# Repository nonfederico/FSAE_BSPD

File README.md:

# FSAE_BSPD
Schema per realizzare il componente BSPD "Brake system plausibility device" seguendo il regolamento di formula Student dell'anno 2024.  
Nel progetto utilizzo il circuito integrato "NE555" per attività universitaria.  
Gli spazi e le piste non sono ottimizzate.  
La documentazione è in italiano ma verrà tradotta in inglese

Schematic for building the BSPD "Brake System Plausibility Device" component according to the Formula Student 2024 regulations. 
In the project, i use the integrated circuit "NE555" for academic activities.
PCB Traces and spaces are not optimized.
The documentation is in Italian but will be translated into English.

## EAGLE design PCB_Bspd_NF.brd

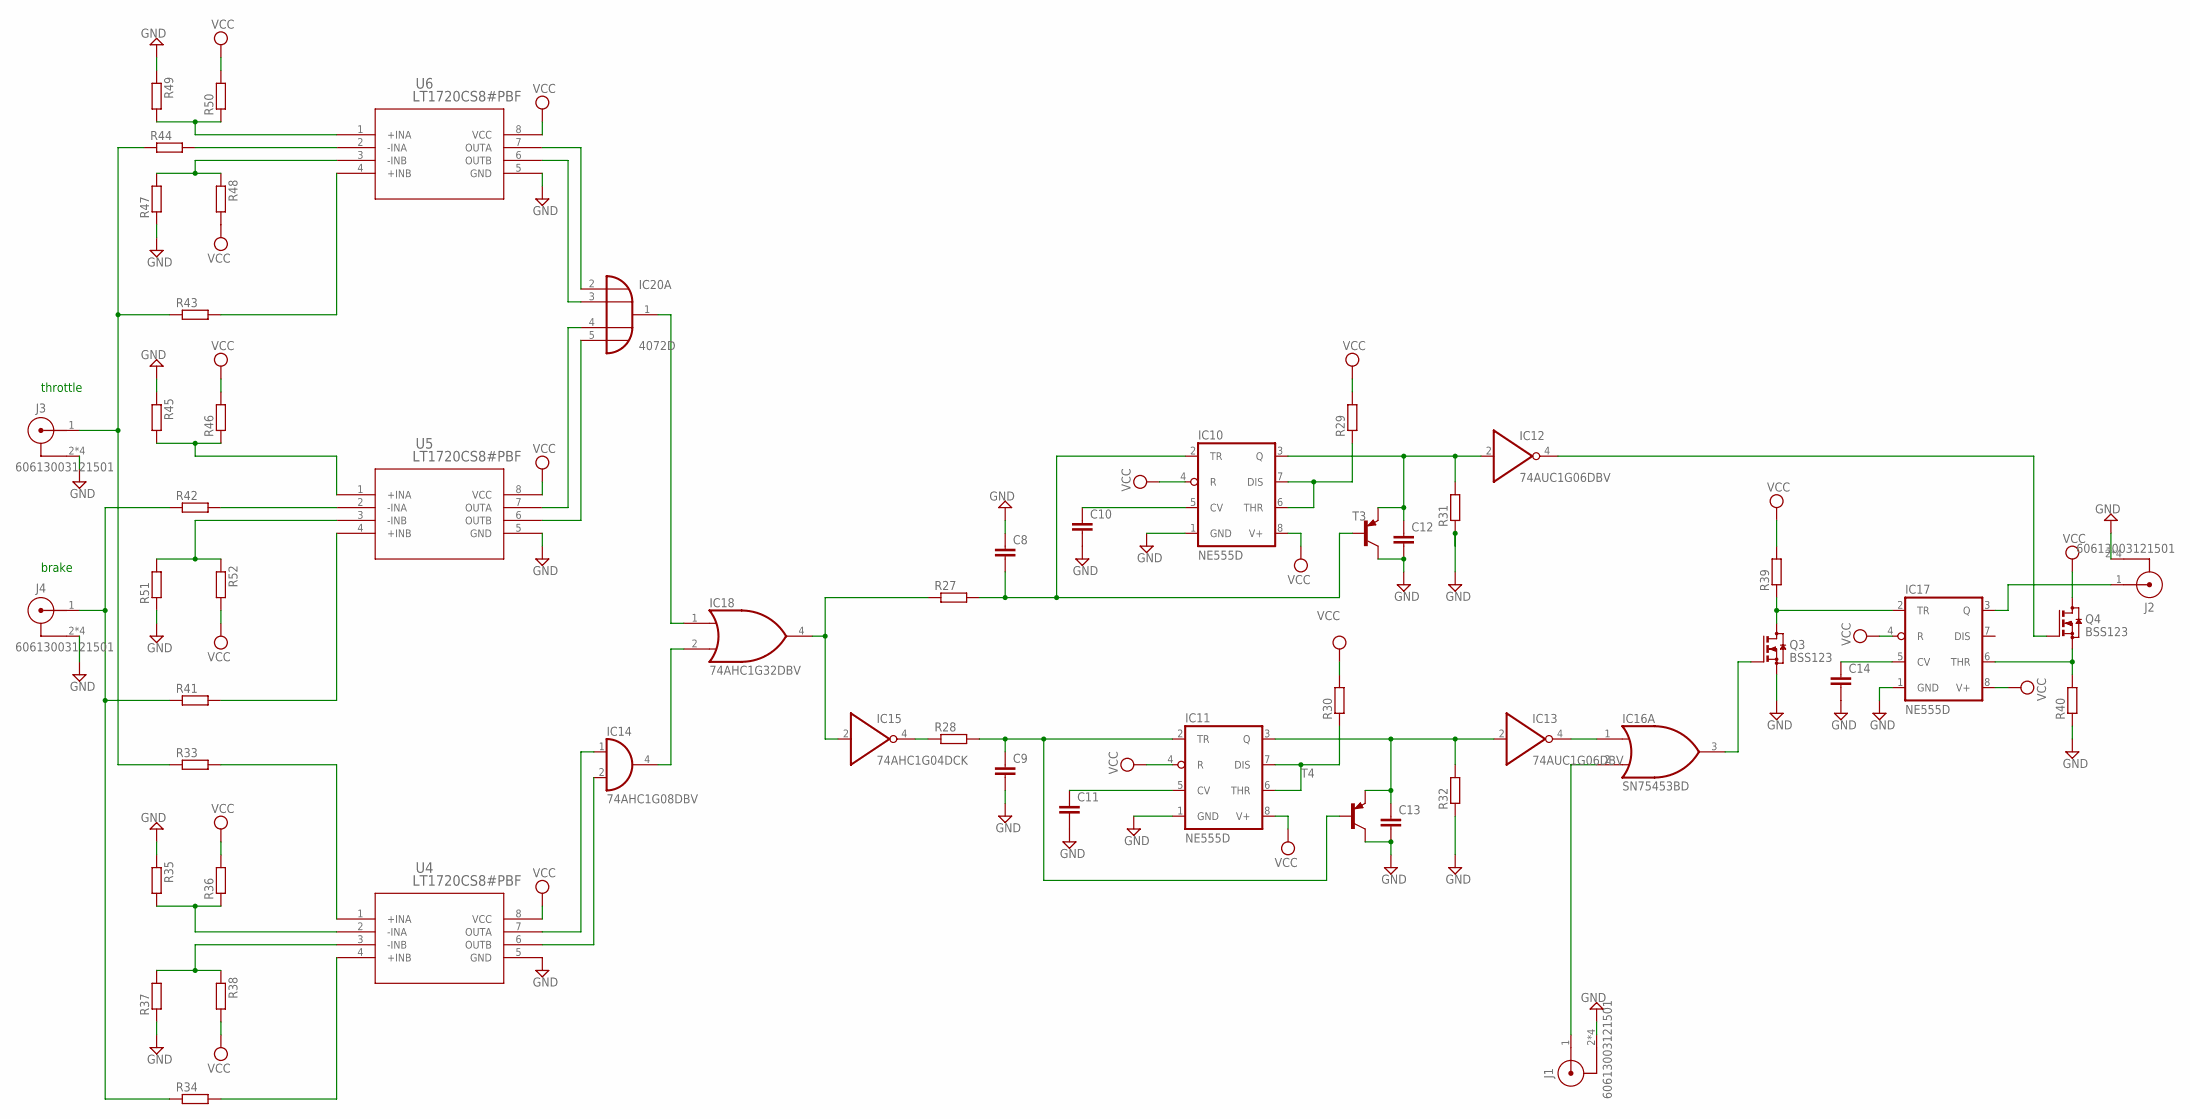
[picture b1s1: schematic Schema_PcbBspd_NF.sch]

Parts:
C8, C9, C10, C11, C12, C13, C14: C2,5-3; C2.5-3
IC10, IC11, IC17: NE555D; SO08
IC12, IC13: 74AUC1G06DBV; SOT23-5
IC14: 74AHC1G08DBV; SOT23-5
IC15: 74AHC1G04DCK; SC70-5
IC16: SN75453BD; D_R-PDSO-G8
IC18: 74AHC1G32DBV; SOT23-5
IC20: 4072D; SO14
J1, J2, J3, J4: 60613003121501
Q3, Q4: BSS123; SOT23
R27, R28, R29, R30, R31, R32, R33, R34, R35, R36, R37, R38, R39, R40, R41, R42, R43, R44, R45, R46, R47, R48, R49, R50, R51, R52: R-EU_R0805; R0805
T3, T4: BC857A-PNP-SOT23-BEC; SOT23-BEC
U4, U5, U6: LT1720CS8#PBF; SO-8_S

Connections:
GND: C8.1, C9.2, C10.2, C11.2, C12.2, C13.2, C14.2, IC10.1 (GND), IC11.1 (GND), IC12.3 (GND), IC13.3 (GND), IC14.3 (GND), IC15.3 (GND), IC16.4 (GND), IC17.1 (GND), IC18.3 (GND), J1.2, J1.3 (2), J1.4 (2), J1.5 (2), J2.2, J2.3 (2), J2.4 (2), J2.5 (2), J3.2, J3.3 (2), J3.4 (2), J3.5 (2), J4.2, J4.3 (2), J4.4 (2), J4.5 (2), Q3.2 (S), R31.1, R32.1, R35.1, R37.1, R40.1, R45.1, R47.1, R49.1, R51.1, T3.C, T4.C, U4.5 (GND), U5.5 (GND), U6.5 (GND)
unnamed: IC13.4 (O), IC16.1 (I0)
unnamed: IC16.3 (O), Q3.1 (G)
unnamed: C10.1, IC10.5 (CV)
unnamed: C11.1, IC11.5 (CV)
unnamed: IC10.6 (THR), IC10.7 (DIS), R29.1
unnamed: IC11.6 (THR), IC11.7 (DIS), R30.1
unnamed: C12.1, IC10.3 (Q), IC12.2 (I), R31.2, T3.E
unnamed: C13.1, IC11.3 (Q), IC13.2 (I), R32.2, T4.E
unnamed: R34.2, U4.4 (+INB)
unnamed: R37.2, R38.1, U4.3 (-INB)
unnamed: R35.2, R36.1, U4.2 (-INA)
unnamed: R33.2, U4.1 (+INA)
unnamed: IC20.2 (I0), U6.7 (OUTA)
unnamed: IC20.3 (I1), U6.6 (OUTB)
unnamed: IC17.6 (THR), Q4.2 (S), R40.2
unnamed: IC16.2 (I1), J1.1
unnamed: IC17.2 (TR), Q3.3 (D), R39.1
unnamed: IC17.3 (Q), J2.1
unnamed: C14.1, IC17.5 (CV)
unnamed: IC12.4 (O), Q4.1 (G)
unnamed: J4.1, R34.1, R41.1, R42.1
unnamed: J3.1, R33.1, R43.1, R44.1
unnamed: R43.2, U6.4 (+INB)
unnamed: R41.2, U5.4 (+INB)
unnamed: R44.2, U6.2 (-INA)
unnamed: R42.2, U5.2 (-INA)
unnamed: R47.2, R48.1, U6.3 (-INB)
unnamed: R49.2, R50.1, U6.1 (+INA)
unnamed: R45.2, R46.1, U5.1 (+INA)
unnamed: IC20.4 (I2), U5.7 (OUTA)
unnamed: IC20.5 (I3), U5.6 (OUTB)
unnamed: IC14.1 (I0), U4.7 (OUTA)
unnamed: IC14.2 (I1), U4.6 (OUTB)
unnamed: IC18.1 (I0), IC20.1 (O)
unnamed: IC14.4 (O), IC18.2 (I1)
unnamed: IC15.2 (I), IC18.4 (O), R27.1
unnamed: IC15.4 (O), R28.1
unnamed: C8.2, IC10.2 (TR), R27.2, T3.B
unnamed: C9.1, IC11.2 (TR), R28.2, T4.B
unnamed: R51.2, R52.1, U5.3 (-INB)
VCC: IC10.4 (R), IC10.8 (V+), IC11.4 (R), IC11.8 (V+), IC12.5 (VCC), IC13.5 (VCC), IC14.5 (VCC), IC15.5 (VCC), IC16.8 (VCC), IC17.4 (R), IC17.8 (V+), IC18.5 (VCC), Q4.3 (D), R29.2, R30.2, R36.2, R38.2, R39.2, R46.2, R48.2, R50.2, R52.2, U4.8 (VCC), U5.8 (VCC), U6.8 (VCC)
VDD: IC20.14 (VDD)
VSS: IC20.7 (VSS)

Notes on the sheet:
brake
throttle

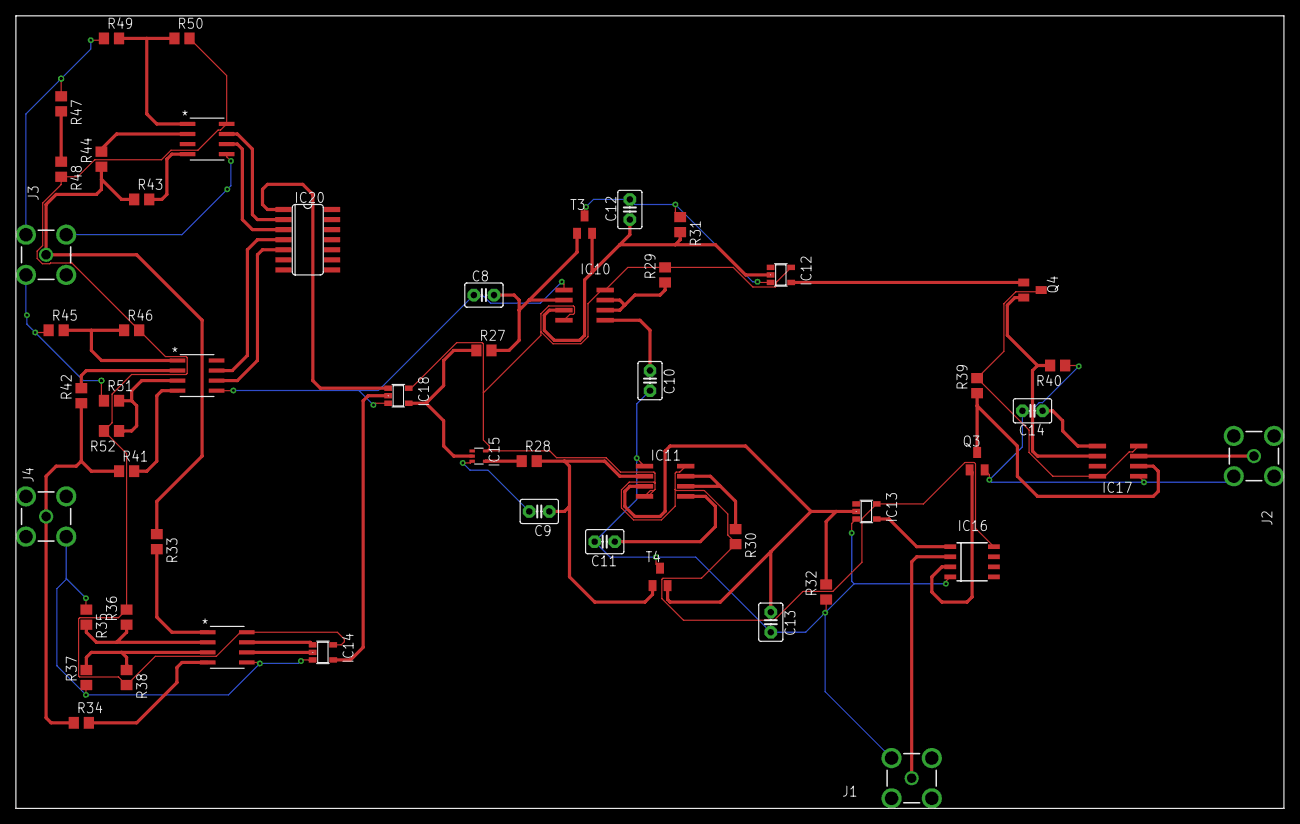
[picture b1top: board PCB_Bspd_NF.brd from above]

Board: 2 copper layers, 160.0 x 100.0 mm, 54 parts (0 on the bottom side), 42 nets.

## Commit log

2025-02-24 Update file
2025-02-24 UPDATE DOC
